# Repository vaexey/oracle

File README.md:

# oracle
PDA device concept  

`TODO: README`

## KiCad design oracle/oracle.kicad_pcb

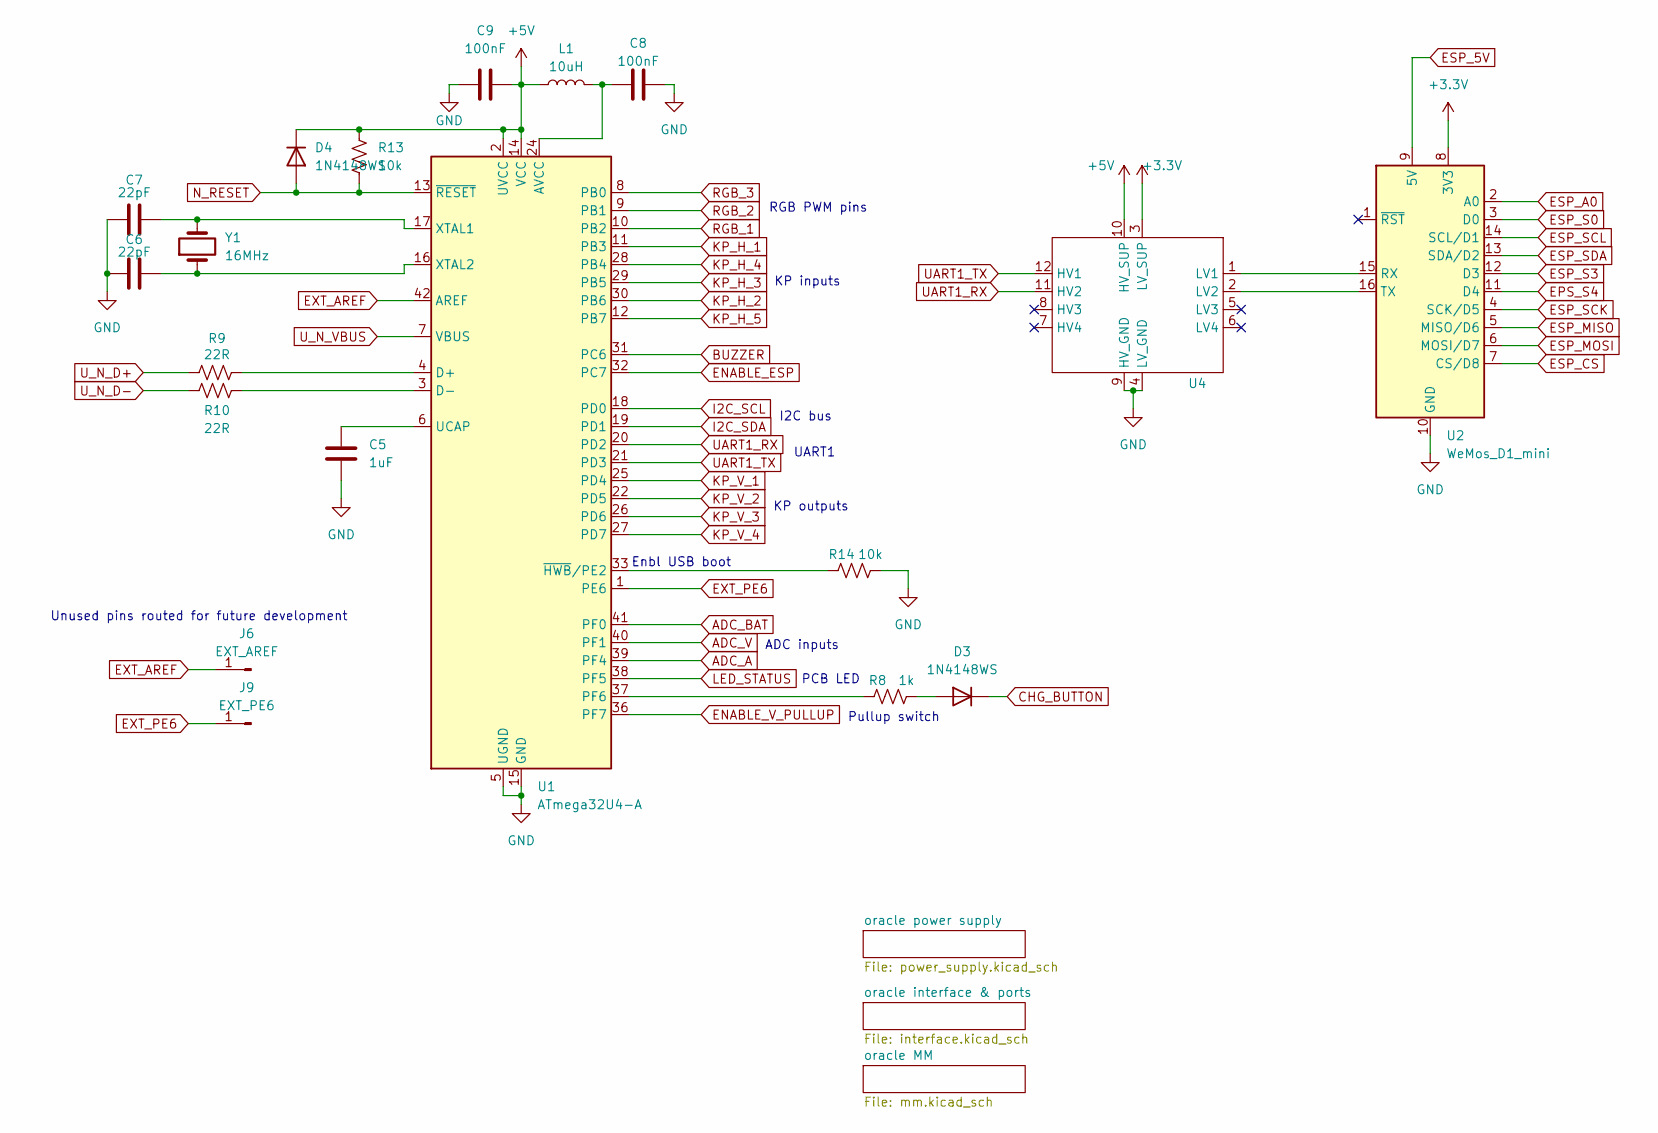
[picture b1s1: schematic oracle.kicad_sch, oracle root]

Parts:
C5: 1uF; C_1210_3225Metric
C6, C7: 22pF; C_0805_2012Metric
C8, C9: 100nF; C_0805_2012Metric
D3, D4: 1N4148WS; D_SOD-323F
J6: EXT_AREF; PinSocket_1x01_P2.54mm_Vertical
J9: EXT_PE6; PinSocket_1x01_P2.54mm_Vertical
L1: 10uH; L_1206_3216Metric
R8: 1k; R_1206_3216Metric
R9, R10: 22R; R_1206_3216Metric
R13, R14: 10k; R_1206_3216Metric
U1: ATmega32U4-A; TQFP-44_10x10mm_P0.8mm
U2: WeMos_D1_mini; WEMOS_D1_mini_light
U4: 4ch_level_shifter_v1
Y1: 16MHz; Crystal_SMD_HC49-SD

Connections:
+3.3V: U2.8 (3V3), U4.3 (LV_SUP)
+5V: C9.2, D4.1 (K), L1.1, R13.1, U1.2 (UVCC), U1.14 (VCC), U1.34 (VCC), U4.10 (HV_SUP); also elsewhere on the board
ADC_A: U1.39 (PF4); also elsewhere on the board
ADC_BAT: U1.41 (PF0); also elsewhere on the board
ADC_V: U1.40 (PF1); also elsewhere on the board
BUZZER: U1.31 (PC6); also elsewhere on the board
CHG_BUTTON: D3.1 (K); also elsewhere on the board
ENABLE_ESP: U1.32 (PC7); also elsewhere on the board
ENABLE_V_PULLUP: U1.36 (PF7); also elsewhere on the board
EPS_S4: U2.11 (D4); also elsewhere on the board
ESP_5V: U2.9 (5V); also elsewhere on the board
ESP_A0: U2.2 (A0); also elsewhere on the board
ESP_CS: U2.7 (CS/D8); also elsewhere on the board
ESP_MISO: U2.5 (MISO/D6); also elsewhere on the board
ESP_MOSI: U2.6 (MOSI/D7); also elsewhere on the board
ESP_S0: U2.3 (D0); also elsewhere on the board
ESP_S3: U2.12 (D3); also elsewhere on the board
ESP_SCK: U2.4 (SCK/D5); also elsewhere on the board
ESP_SCL: U2.14 (SCL/D1); also elsewhere on the board
ESP_SDA: U2.13 (SDA/D2); also elsewhere on the board
EXT_AREF: J6.1, U1.42 (AREF)
EXT_PE6: J9.1, U1.1 (PE6)
GND: C5.2, C6.1, C7.1, C8.2, C9.1, R14.2, U1.5 (UGND), U1.15 (GND), U1.23 (GND), U1.35 (GND), U1.43 (GND), U2.10 (GND), U4.4 (LV_GND), U4.9 (HV_GND); also elsewhere on the board
I2C_SCL: U1.18 (PD0); also elsewhere on the board
I2C_SDA: U1.19 (PD1); also elsewhere on the board
KP_H_1: U1.11 (PB3); also elsewhere on the board
KP_H_2: U1.30 (PB6); also elsewhere on the board
KP_H_3: U1.29 (PB5); also elsewhere on the board
KP_H_4: U1.28 (PB4); also elsewhere on the board
KP_H_5: U1.12 (PB7); also elsewhere on the board
KP_V_1: U1.25 (PD4); also elsewhere on the board
KP_V_2: U1.22 (PD5); also elsewhere on the board
KP_V_3: U1.26 (PD6); also elsewhere on the board
KP_V_4: U1.27 (PD7); also elsewhere on the board
LED_STATUS: U1.38 (PF5); also elsewhere on the board
N_RESET: D4.2 (A), R13.2, U1.13 (~RESET)
unnamed: C8.1, L1.2, U1.24 (AVCC), U1.44 (AVCC)
unnamed: D3.2 (A), R8.2
unnamed: R9.2, U1.4 (D+)
unnamed: R10.2, U1.3 (D-)
unnamed: R8.1, U1.37 (PF6)
unnamed: C5.1, U1.6 (UCAP)
unnamed: C7.2, U1.17 (XTAL1), Y1.2
unnamed: C6.2, U1.16 (XTAL2), Y1.1
unnamed: R14.1, U1.33 (~HWB/PE2)
unnamed: U2.15 (RX), U4.1 (LV1)
unnamed: U2.16 (TX), U4.2 (LV2)
RGB_1: U1.10 (PB2); also elsewhere on the board
RGB_2: U1.9 (PB1); also elsewhere on the board
RGB_3: U1.8 (PB0); also elsewhere on the board
UART1_RX: U1.20 (PD2), U4.11 (HV2)
UART1_TX: U1.21 (PD3), U4.12 (HV1)
U_N_D+: R9.1; also elsewhere on the board
U_N_D-: R10.1; also elsewhere on the board
U_N_VBUS: U1.7 (VBUS); also elsewhere on the board

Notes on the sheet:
RGB PWM pins
Pullup switch
ADC inputs
Unused pins routed for future development
I2C bus
KP outputs
KP inputs
UART1
PCB LED
Enbl USB boot

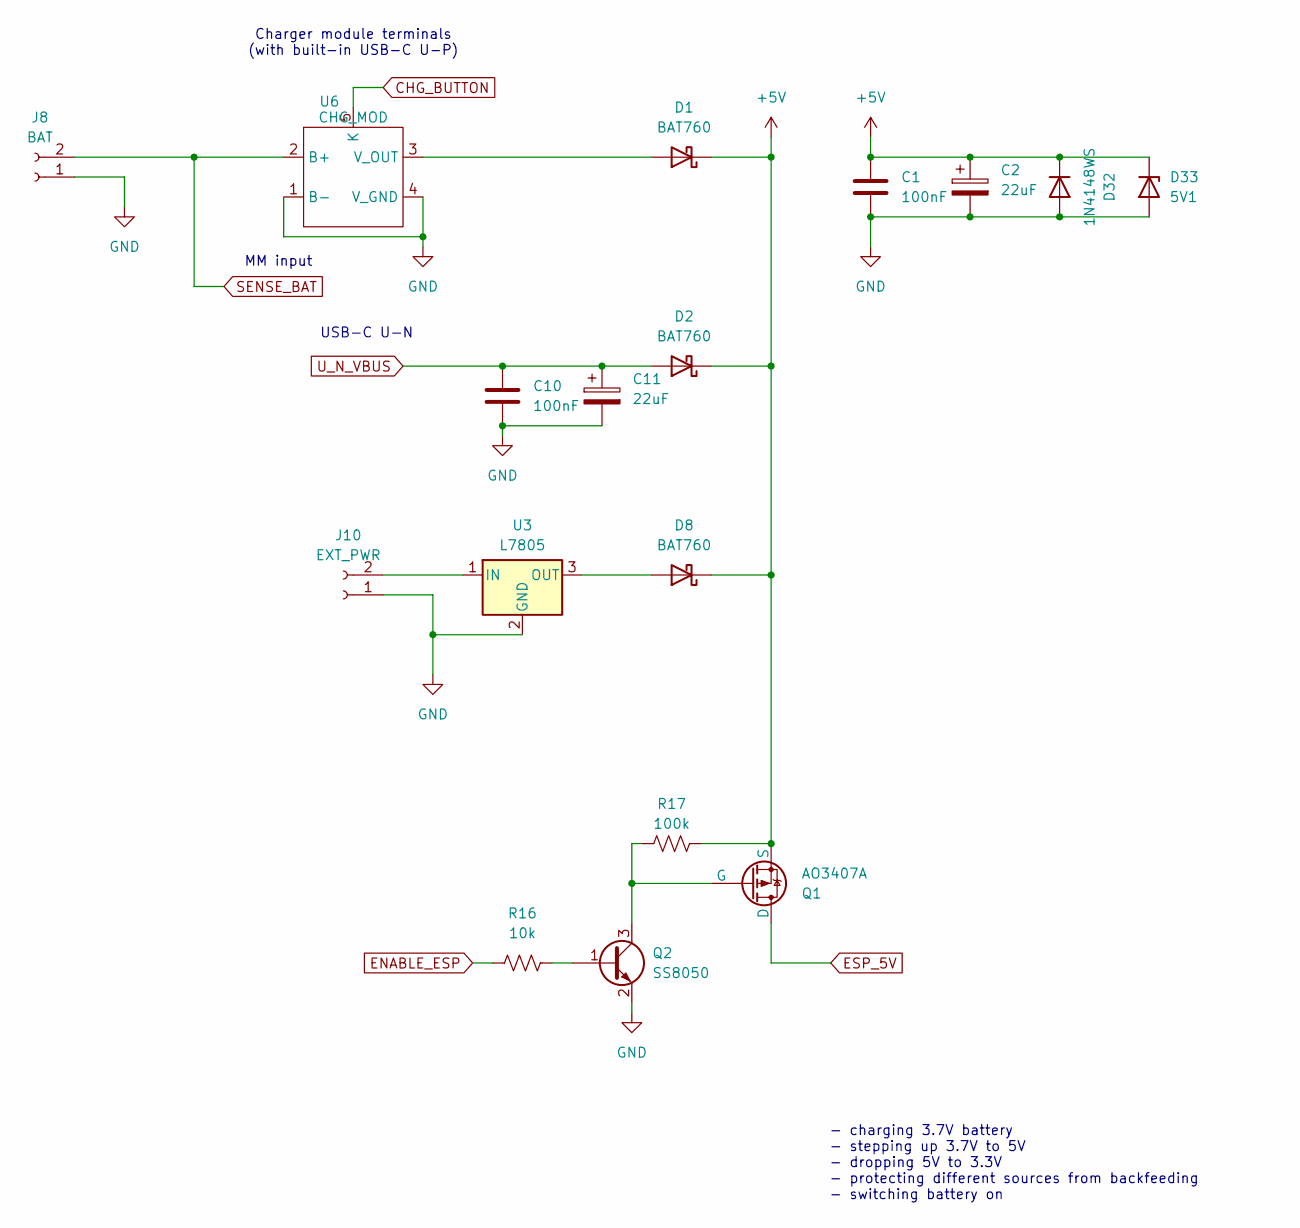
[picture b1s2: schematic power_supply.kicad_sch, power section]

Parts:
C1, C10: 100nF; C_0805_2012Metric
C2, C11: 22uF; C_1210_3225Metric
D1, D2, D8: BAT760; D_SOD-323F
D32: 1N4148WS; D_SOD-323F
D33: 5V1; D_DO-15_P10.16mm_Horizontal
J8: BAT; PinHeader_2x01_P2.54mm_Vertical
J10: EXT_PWR; PinHeader_2x01_P2.54mm_Vertical
Q1: AO3407A; TSOT-23
Q2: SS8050; SOT-23
R16: 10k; R_1206_3216Metric
R17: 100k; R_1206_3216Metric
U3: L7805; TO-252-2
U6: CHG_MOD; lipo_chg_module

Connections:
+5V: C1.1, C2.1, D1.1 (K), D2.1 (K), D8.1 (K), D32.1 (K), D33.1 (K), Q1.3 (S), R17.1; also elsewhere on the board
CHG_BUTTON: U6.5 (K); also elsewhere on the board
ENABLE_ESP: R16.2; also elsewhere on the board
ESP_5V: Q1.1 (D); also elsewhere on the board
GND: C1.2, C2.2, C10.2, C11.2, D32.2 (A), D33.2 (A), J8.1, J10.1, Q2.2 (E), U3.2 (GND), U6.1 (B-), U6.4 (V_GND); also elsewhere on the board
unnamed: D1.2 (A), U6.3 (V_OUT)
unnamed: D8.2 (A), U3.3 (OUT)
unnamed: J10.2, U3.1 (IN)
unnamed: Q1.2 (G), Q2.3 (C), R17.2
unnamed: Q2.1 (B), R16.1
SENSE_BAT: J8.2, U6.2 (B+); also elsewhere on the board
U_N_VBUS: C10.1, C11.1, D2.2 (A); also elsewhere on the board

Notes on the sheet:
- charging 3.7V battery - stepping up 3.7V to 5V - dropping 5V to 3.3V - protecting different sources from backfeeding - switching battery on
MM input
USB-C U-N
Charger module terminals (with built-in USB-C U-P)

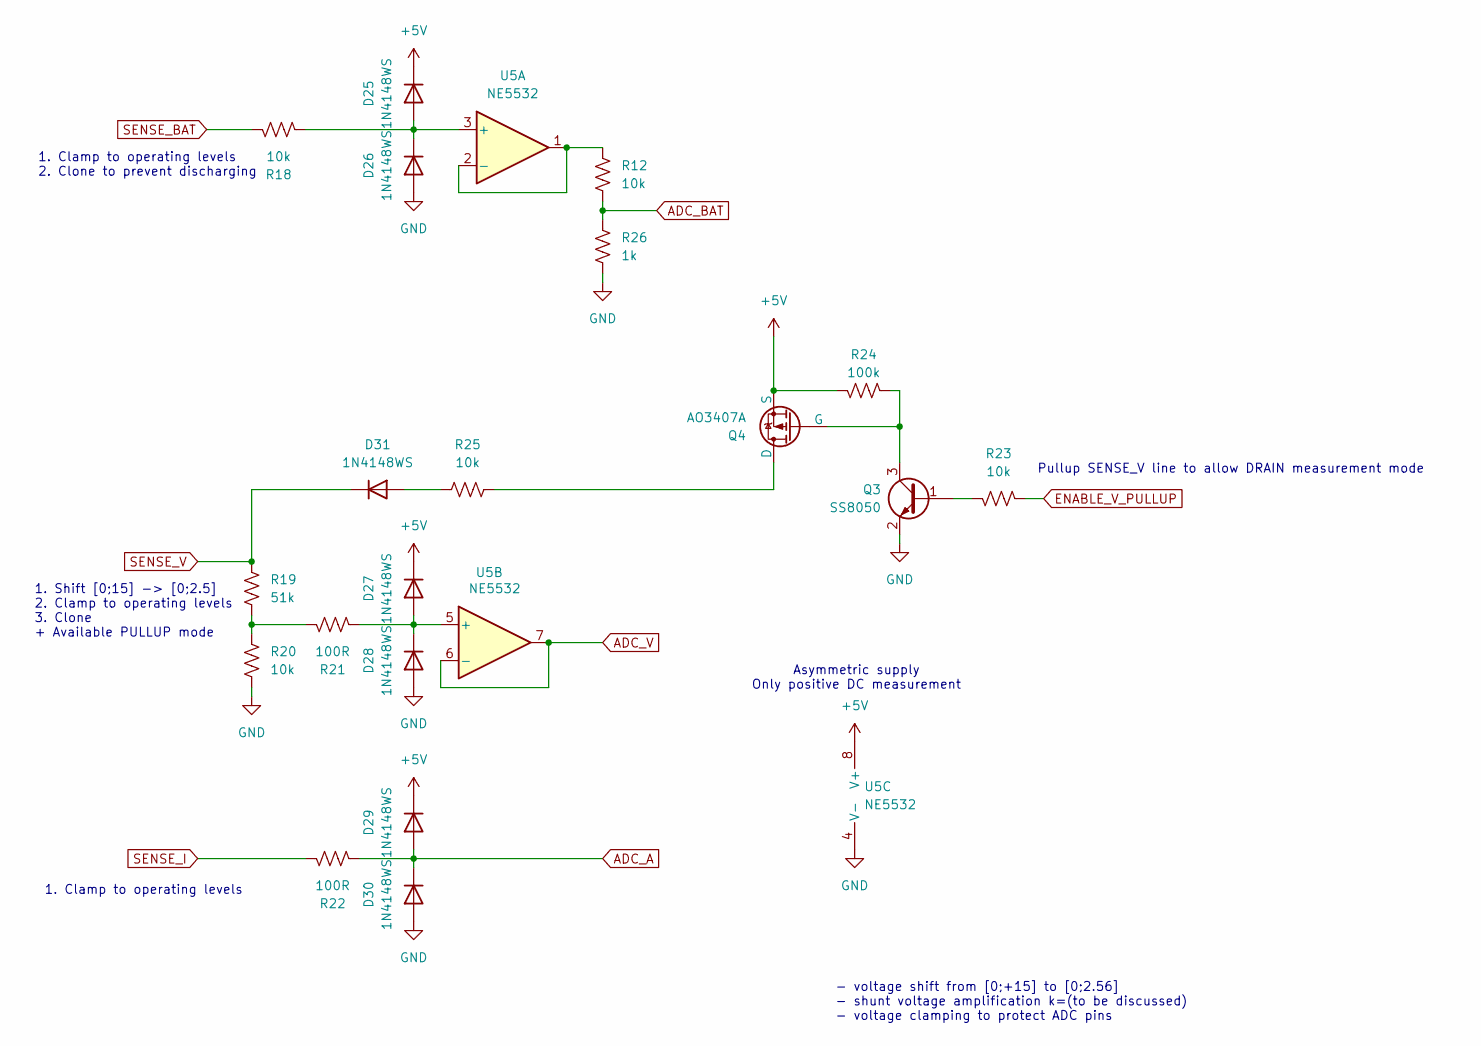
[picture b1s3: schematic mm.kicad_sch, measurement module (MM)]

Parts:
D25, D26, D27, D28, D29, D30, D31: 1N4148WS; D_SOD-323F
Q3: SS8050; SOT-23
Q4: AO3407A; TSOT-23
R12, R18, R20, R23, R25: 10k; R_1206_3216Metric
R19: 51k; R_1206_3216Metric
R21, R22: 100R; R_1206_3216Metric
R24: 100k; R_1206_3216Metric
R26: 1k; R_1206_3216Metric
U5: NE5532; SO-8_5.3x6.2mm_P1.27mm

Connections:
+5V: D25.1 (K), D27.1 (K), D29.1 (K), Q4.3 (S), R24.1, U5.8 (V+); also elsewhere on the board
ADC_A: D29.2 (A), D30.1 (K), R22.2; also elsewhere on the board
ADC_BAT: R12.2, R26.1; also elsewhere on the board
ADC_V: U5.6 (-), U5.7; also elsewhere on the board
ENABLE_V_PULLUP: R23.2; also elsewhere on the board
GND: D26.2 (A), D28.2 (A), D30.2 (A), Q3.2 (E), R20.2, R26.2, U5.4 (V-); also elsewhere on the board
unnamed: D25.2 (A), D26.1 (K), R18.2, U5.3 (+)
unnamed: D27.2 (A), D28.1 (K), R21.2, U5.5 (+)
unnamed: D31.2 (A), R25.1
unnamed: Q3.1 (B), R23.1
unnamed: Q3.3 (C), Q4.2 (G), R24.2
unnamed: Q4.1 (D), R25.2
unnamed: R19.2, R20.1, R21.1
unnamed: R12.1, U5.1, U5.2 (-)
SENSE_BAT: R18.1; also elsewhere on the board
SENSE_I: R22.1; also elsewhere on the board
SENSE_V: D31.1 (K), R19.1; also elsewhere on the board

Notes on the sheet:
1. Clamp to operating levels 2. Clone to prevent discharging
1. Clamp to operating levels
1. Shift [0;15] -> [0;2.5] 2. Clamp to operating levels 3. Clone + Available PULLUP mode
- voltage shift from [0;+15] to [0;2.56] - shunt voltage amplification k=(to be discussed) - voltage clamping to protect ADC pins
Pullup SENSE_V line to allow DRAIN measurement mode
Asymmetric supply Only positive DC measurement

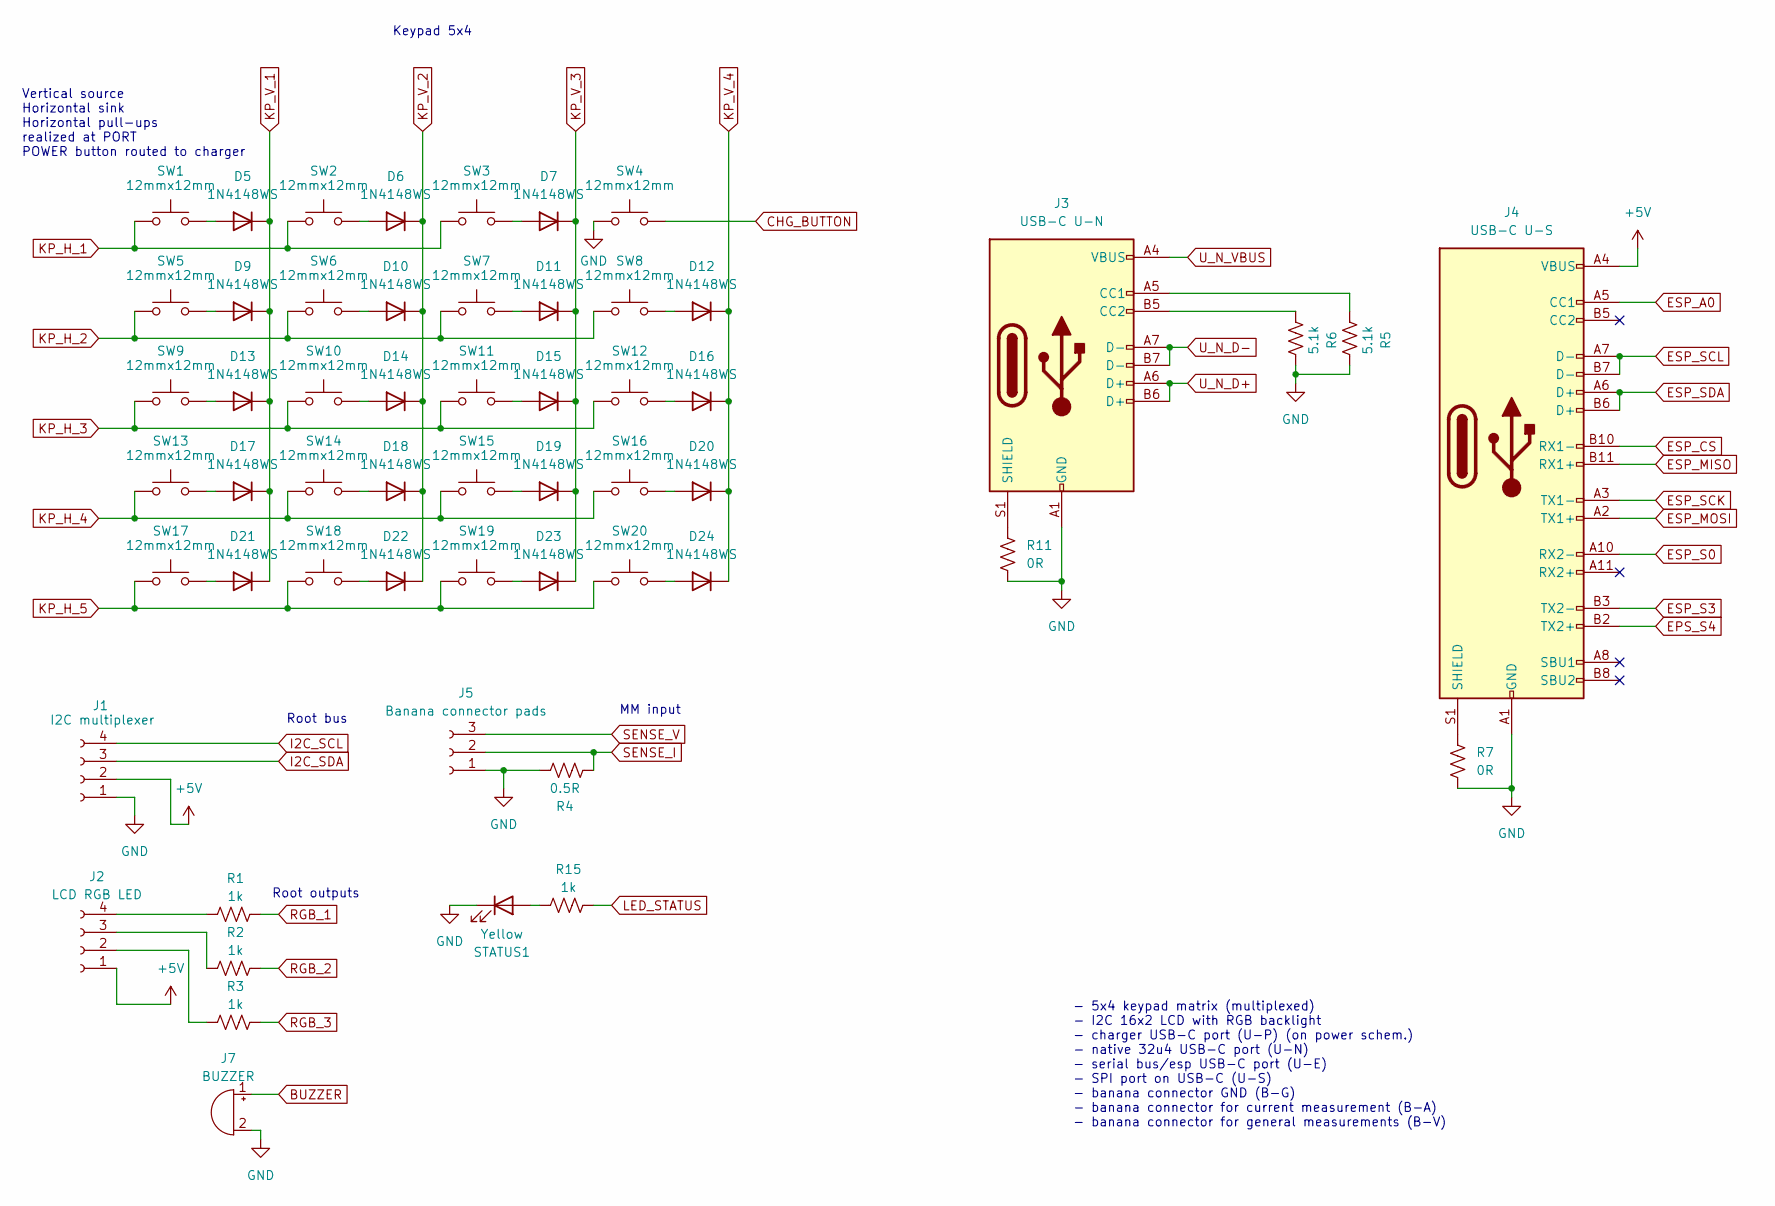
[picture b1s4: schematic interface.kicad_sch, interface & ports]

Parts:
D5, D6, D7, D9, D10, D11, D12, D13, D14, D15, D16, D17, D18, D19, D20, D21, D22, D23, D24: 1N4148WS; D_SOD-323F
J1: I2C multiplexer; PinSocket_1x04_P2.54mm_Vertical
J2: LCD RGB LED; PinSocket_1x04_P2.54mm_Vertical
J3: USB-C U-N; USB_C_Receptacle_GCT_USB4105-xx-A_16P_TopMnt_Horizontal
J4: USB-C U-S; USB_C_Receptacle_Amphenol_12401548E4-2A
J5: Banana connector pads; PinSocket_1x03_P2.54mm_Vertical
J7: BUZZER; PinHeader_1x02_P2.54mm_Vertical
R1, R2, R3, R15: 1k; R_1206_3216Metric
R4: 0.5R; R_1206_3216Metric
R5, R6: 5.1k; R_1206_3216Metric
R7, R11: 0R; R_1206_3216Metric
STATUS1: Yellow; LED_D3.0mm
SW1, SW2, SW3, SW4, SW5, SW6, SW7, SW8, SW9, SW10, SW11, SW12, SW13, SW14, SW15, SW16, SW17, SW18, SW19, SW20: 12mmx12mm; SW_PUSH-12mm

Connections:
+5V: J1.2, J2.1, J4.A4 (VBUS), J4.A9 (VBUS), J4.B4 (VBUS), J4.B9 (VBUS); also elsewhere on the board
BUZZER: J7.1 (+); also elsewhere on the board
CHG_BUTTON: SW4.2; also elsewhere on the board
EPS_S4: J4.B2 (TX2+); also elsewhere on the board
ESP_A0: J4.A5 (CC1); also elsewhere on the board
ESP_CS: J4.B10 (RX1-); also elsewhere on the board
ESP_MISO: J4.B11 (RX1+); also elsewhere on the board
ESP_MOSI: J4.A2 (TX1+); also elsewhere on the board
ESP_S0: J4.A10 (RX2-); also elsewhere on the board
ESP_S3: J4.B3 (TX2-); also elsewhere on the board
ESP_SCK: J4.A3 (TX1-); also elsewhere on the board
ESP_SCL: J4.A7 (D-), J4.B7 (D-); also elsewhere on the board
ESP_SDA: J4.A6 (D+), J4.B6 (D+); also elsewhere on the board
GND: J1.1, J3.A1 (GND), J3.A12 (GND), J3.B1 (GND), J3.B12 (GND), J4.A1 (GND), J4.A12 (GND), J4.B1 (GND), J4.B12 (GND), J5.1, J7.2 (-), R4.2, R5.2, R6.2, R7.2, R11.2, STATUS1.1 (K), SW4.1; also elsewhere on the board
I2C_SCL: J1.4; also elsewhere on the board
I2C_SDA: J1.3; also elsewhere on the board
KP_H_1: SW1.1, SW2.1, SW3.1; also elsewhere on the board
KP_H_2: SW5.1, SW6.1, SW7.1, SW8.1; also elsewhere on the board
KP_H_3: SW9.1, SW10.1, SW11.1, SW12.1; also elsewhere on the board
KP_H_4: SW13.1, SW14.1, SW15.1, SW16.1; also elsewhere on the board
KP_H_5: SW17.1, SW18.1, SW19.1, SW20.1; also elsewhere on the board
KP_V_1: D5.1 (K), D9.1 (K), D13.1 (K), D17.1 (K), D21.1 (K); also elsewhere on the board
KP_V_2: D6.1 (K), D10.1 (K), D14.1 (K), D18.1 (K), D22.1 (K); also elsewhere on the board
KP_V_3: D7.1 (K), D11.1 (K), D15.1 (K), D19.1 (K), D23.1 (K); also elsewhere on the board
KP_V_4: D12.1 (K), D16.1 (K), D20.1 (K), D24.1 (K); also elsewhere on the board
LED_STATUS: R15.2; also elsewhere on the board
unnamed: D5.2 (A), SW1.2
unnamed: D6.2 (A), SW2.2
unnamed: D7.2 (A), SW3.2
unnamed: D9.2 (A), SW5.2
unnamed: D10.2 (A), SW6.2
unnamed: D11.2 (A), SW7.2
unnamed: D12.2 (A), SW8.2
unnamed: D13.2 (A), SW9.2
unnamed: D14.2 (A), SW10.2
unnamed: D15.2 (A), SW11.2
unnamed: D16.2 (A), SW12.2
unnamed: D17.2 (A), SW13.2
unnamed: D18.2 (A), SW14.2
unnamed: D19.2 (A), SW15.2
unnamed: D20.2 (A), SW16.2
unnamed: D21.2 (A), SW17.2
unnamed: D22.2 (A), SW18.2
unnamed: D23.2 (A), SW19.2
unnamed: D24.2 (A), SW20.2
unnamed: J2.2, R3.1
unnamed: J2.3, R2.1
unnamed: J2.4, R1.1
unnamed: J3.A5 (CC1), R5.1
unnamed: J3.B5 (CC2), R6.1
unnamed: J3.S1 (SHIELD), R11.1
unnamed: J4.S1 (SHIELD), R7.1
unnamed: R15.1, STATUS1.2 (A)
RGB_1: R1.2; also elsewhere on the board
RGB_2: R2.2; also elsewhere on the board
RGB_3: R3.2; also elsewhere on the board
SENSE_I: J5.2, R4.1; also elsewhere on the board
SENSE_V: J5.3; also elsewhere on the board
U_N_D+: J3.A6 (D+), J3.B6 (D+); also elsewhere on the board
U_N_D-: J3.A7 (D-), J3.B7 (D-); also elsewhere on the board
U_N_VBUS: J3.A4 (VBUS), J3.A9 (VBUS), J3.B4 (VBUS), J3.B9 (VBUS); also elsewhere on the board

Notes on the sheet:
Root bus
Root outputs
- 5x4 keypad matrix (multiplexed) - I2C 16x2 LCD with RGB backlight - charger USB-C port (U-P) (on power schem.) - native 32u4 USB-C port (U-N) - serial bus/esp USB-C port (U-E) - SPI port on USB-C (U-S) - banana connector GND (B-G) - banana connector for current measurement (B-A) - banana connecto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
MM input
Vertical source Horizontal sink Horizontal pull-ups realized at PORT POWER button routed to charger
Keypad 5x4

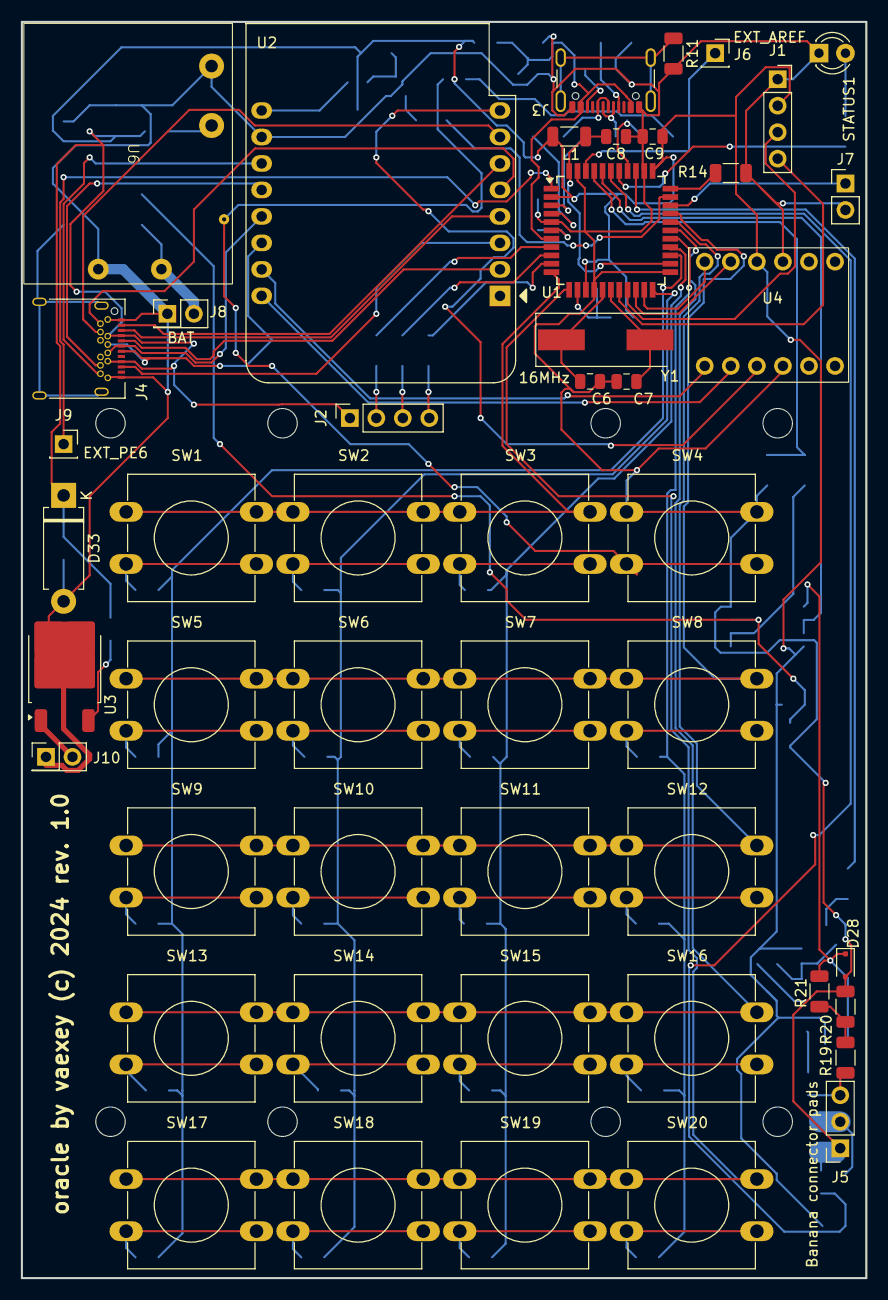
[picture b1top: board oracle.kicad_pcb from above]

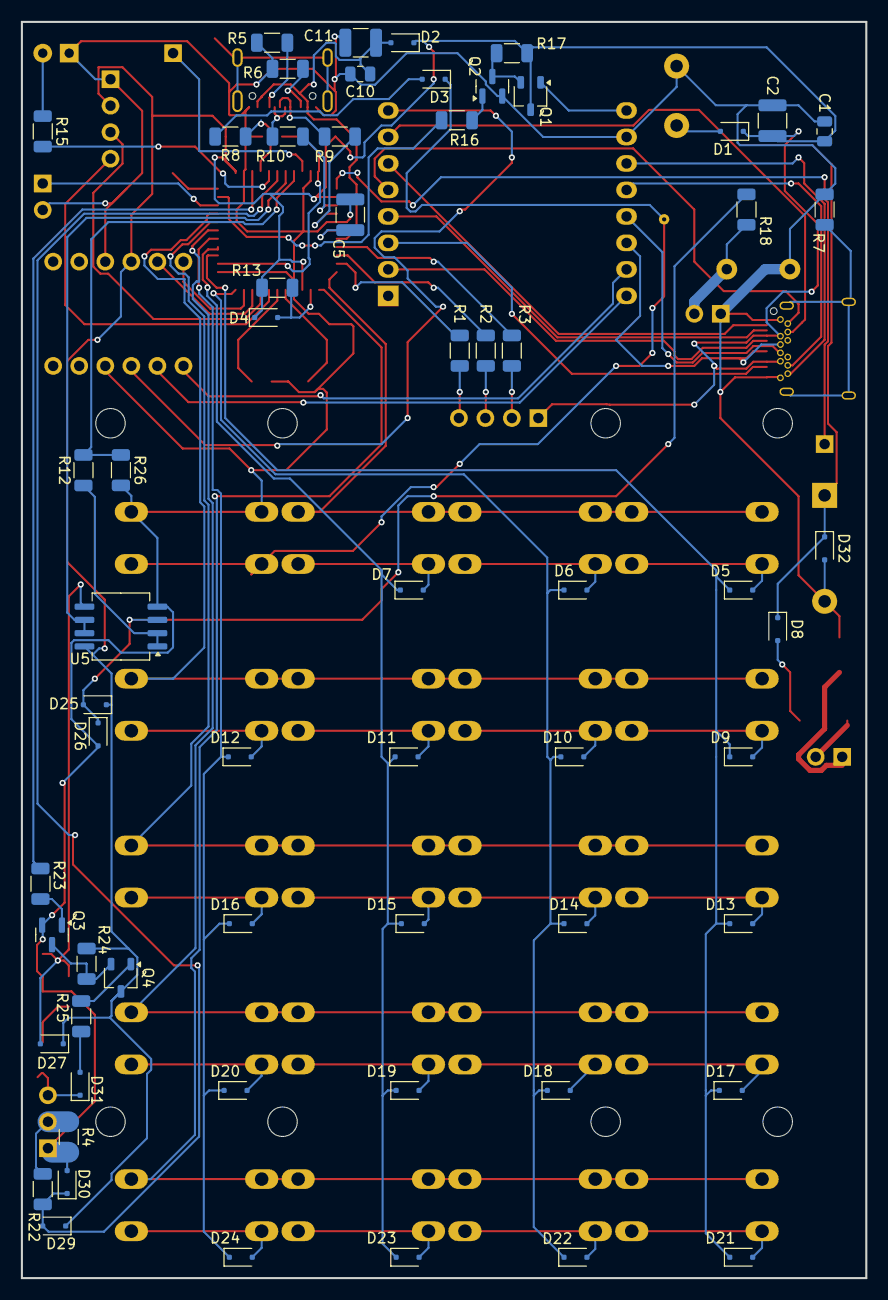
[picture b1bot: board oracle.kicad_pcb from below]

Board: 2 copper layers, 81.0 x 120.5 mm, 111 parts (62 on the bottom side), 98 nets.

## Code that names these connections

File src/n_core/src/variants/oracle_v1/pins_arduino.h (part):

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
// ATMEL ATMEGA32U4 / ARDUINO LEONARDO
//
// D0				PD2					RXD1/INT2
// D1				PD3					TXD1/INT3
// D2				PD1		SDA			SDA/INT1
// D3#				PD0		PWM8/SCL	OC0B/SCL/INT0
// D4		A6		PD4					ADC8
// D5#				PC6		???			OC3A/#OC4A
// D6#		A7		PD7		FastPWM		#OC4D/ADC10
// D7				PE6					INT6/AIN0
//
// D8		A8		PB4					ADC11/PCINT4
// D9#		A9		PB5		PWM16		OC1A/#OC4B/ADC12/PCINT5
// D10#		A10		PB6		PWM16		OC1B/0c4B/ADC13/PCINT6
// D11#				PB7		PWM8/16		0C0A/OC1C/#RTS/PCINT7
// D12		A11		PD6					T1/#OC4D/ADC9
// D13#				PC7		PWM10		CLK0/OC4A
//
// A0		D18		PF7					ADC7
// A1		D19		PF6					ADC6
// A2		D20 	PF5					ADC5
// A3		D21 	PF4					ADC4
// A4		D22		PF1					ADC1
// A5		D23 	PF0					ADC0
//
// New pins D14..D17 to map SPI port to digital pins
//
// MISO		D14		PB3					MISO,PCINT3
// SCK		D15		PB1					SCK,PCINT1
// MOSI		D16		PB2					MOSI,PCINT2
// SS		D17		PB0					RXLED,SS/PCINT0
//
// TXLED	D30		PD5					XCK1
// RXLED	D17	    PB0
// HWB				PE2					HWB

// these arrays map port names (e.g. port B) to the
// appropriate addresses for various functions (e.g. reading
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};

const uint8_t PROGMEM digital_pin_to_port_PGM[] = {
	PD, // D0 - PD2
	PD,	// D1 - PD3
	PD, // D2 - PD1
	PD,	// D3 - PD0
	PD,	// D4 - PD4
	PC, // D5 - PC6
	PD, // D6 - PD7
	PE, // D7 - PE6
	
	PB, // D8 - PB4
	PB,	// D9 - PB5
	PB, // D10 - PB6
	PB,	// D11 - PB7
	PD, // D12 - PD6
	PC, // D13 - PC7
	
	PB,	// D14 - MISO - PB3
	PB,	// D15 - SCK - PB1
	PB,	// D16 - MOSI - PB2
	PB,	// D17 - SS - PB0
	
	PF,	// D18 - A0 - PF7
	PF, // D19 - A1 - PF6
	PF, // D20 - A2 - PF5
	PF, // D21 - A3 - PF4
	PF, // D22 - A4 - PF1
	PF, // D23 - A5 - PF0
	
	PD, // D24 / D4 - A6 - PD4
	PD, // D25 / D6 - A7 - PD7
	PB, // D26 / D8 - A8 - PB4
	PB, // D27 / D9 - A9 - PB5
	PB, // D28 / D10 - A10 - PB6
	PD, // D29 / D12 - A11 - PD6
	PD, // D30 / TX Led - PD5
};

const uint8_t PROGMEM digital_pin_to_bit_mask_PGM[] = {
	_BV(2), // D0 - PD2
	_BV(3),	// D1 - PD3
	_BV(1), // D2 - PD1
	_BV(0),	// D3 - PD0
	_BV(4),	// D4 - PD4
	_BV(6), // D5 - PC6
	_BV(7), // D6 - PD7
	_BV(6), // D7 - PE6
	
	_BV(4), // D8 - PB4
	_BV(5),	// D9 - PB5
	_BV(6), // D10 - PB6
	_BV(7),	// D11 - PB7
	_BV(6), // D12 - PD6
	_BV(7), // D13 - PC7
	
	_BV(3),	// D14 - MISO - PB3
	_BV(1),	// D15 - SCK - PB1
	_BV(2),	// D16 - MOSI - PB2
	_BV(0),	// D17 - SS - PB0
	
	_BV(7),	// D18 - A0 - PF7
	_BV(6), // D19 - A1 - PF6
	_BV(5), // D20 - A2 - PF5
	_BV(4), // D21 - A3 - PF4
	_BV(1), // D22 - A4 - PF1
	_BV(0), // D23 - A5 - PF0
	
	_BV(4), // D24 / D4 - A6 - PD4
	_BV(7), // D25 / D6 - A7 - PD7
	_BV(4), // D26 / D8 - A8 - PB4
	_BV(5), // D27 / D9 - A9 - PB5
	_BV(6), // D28 / D10 - A10 - PB6
	_BV(6), // D29 / D12 - A11 - PD6
	_BV(5), // D30 / TX Led - PD5
};

const uint8_t PROGMEM digital_pin_to_timer_PGM[] = {
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};

const uint8_t PROGMEM analog_pin_to_channel_PGM[] = {
	7,	// A0				PF7					ADC7
	6,	// A1				PF6					ADC6	
	5,	// A2				PF5					ADC5	
	4,	// A3				PF4					ADC4
	1,	// A4				PF1					ADC1	
	0,	// A5				PF0					ADC0	
	8,	// A6		D4		PD4					ADC8
	10,	// A7		D6		PD7					ADC10
	11,	// A8		D8		PB4					ADC11
	12,	// A9		D9		PB5					ADC12
	13,	// A10		D10		PB6					ADC13
	9	// A11		D12		PD6					ADC9
};

#endif /* ARDUINO_MAIN */
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
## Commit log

2024-11-12 Project init
2024-11-30 add n_core firmware add e_core firmware stub update PCB
2024-12-03 add e_core firmware stub add n_core full I/O serial support
2025-01-16 add e_core sample apps add keypad svg minor integration changes

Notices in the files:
src/n_core/src/variants/oracle_v1/pins_arduino.h:
Copyright (c) 2007 David A. Mellis
Public License along with this library; if not, write to the
Free Software Foundation, Inc., 59 Temple Place, Suite 330,
Boston, MA  02111-1307  USA
oracle/oracle.kicad_pcb:
oracle by vaexey (c) 2024 rev. 1.0
